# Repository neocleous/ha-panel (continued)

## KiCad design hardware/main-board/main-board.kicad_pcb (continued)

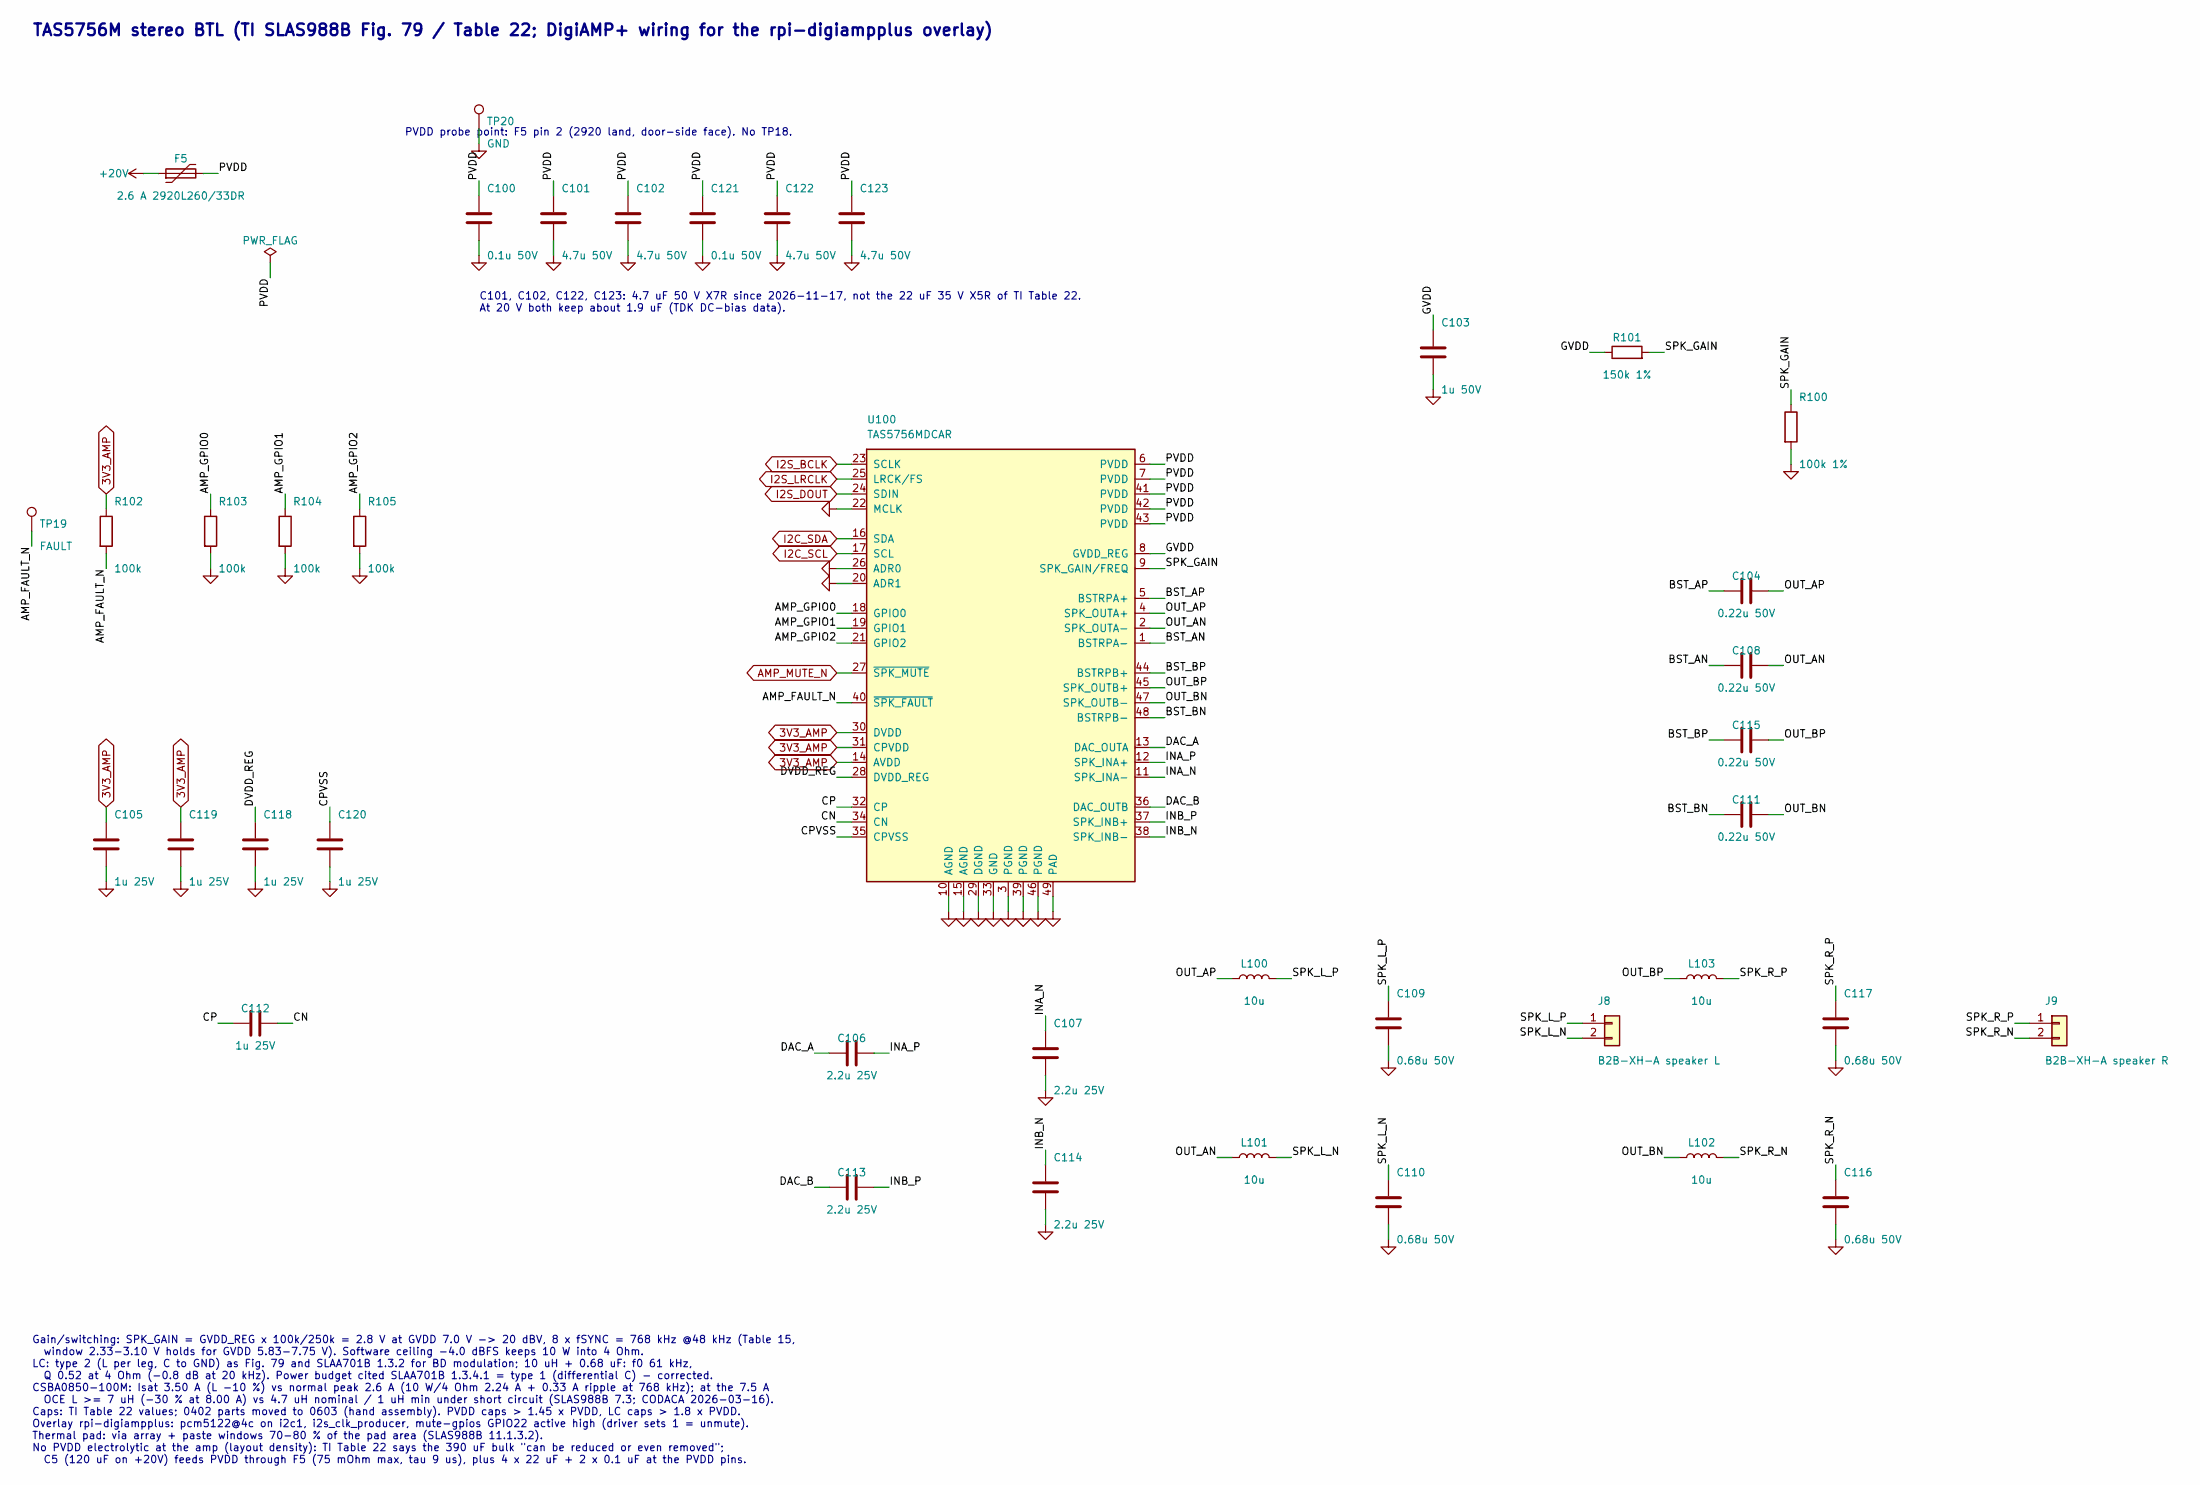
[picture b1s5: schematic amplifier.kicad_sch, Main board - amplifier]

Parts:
C100, C121: 0.1u 50V; C_0603_1608Metric; MPN CC0603KRX7R9BB104; DigiKey 311-1344-1-ND
C101, C102, C122, C123: 4.7u 50V; C_0805_2012Metric; MPN C2012X7R1H475K125AC; DigiKey 445-C2012X7R1H475K125ACCT-ND
C103: 1u 50V; C_0603_1608Metric; MPN UMK107AB7105KA-T; DigiKey 587-3247-1-ND
C104, C108, C111, C115: 0.22u 50V; C_0603_1608Metric; MPN CL10B224KB8NNNC; DigiKey 1276-CL10B224KB8NNNCCT-ND
C105, C112, C118, C119, C120: 1u 25V; C_0603_1608Metric; MPN CC0603KRX7R8BB105; DigiKey 311-1802-1-ND
C106, C107, C113, C114: 2.2u 25V; C_0603_1608Metric; MPN CC0603KRX7R7BB225; DigiKey 311-3490-1-ND
C109, C110, C116, C117: 0.68u 50V; C_0805_2012Metric; MPN CL21B684KBFVPNE; DigiKey 1276-7009-1-ND
F5: 2.6 A 2920L260/33DR; Fuse_2920_7451Metric; MPN 2920L260/33DR; DigiKey 18-2920L260/33DRCT-ND
J8: B2B-XH-A speaker L; JST_XH_B2B-XH-A_1x02_P2.50mm_Vertical; MPN B2B-XH-A; DigiKey 455-B2B-XH-A-ND
J9: B2B-XH-A speaker R; JST_XH_B2B-XH-A_1x02_P2.50mm_Vertical; MPN B2B-XH-A; DigiKey 455-B2B-XH-A-ND
L100, L101, L102, L103: 10u; L_Codaca_CSBA0850; MPN CSBA0850-100M; DigiKey 4044-CSBA0850-100MCT-ND
R100: 100k 1%; R_0603_1608Metric; MPN RMCF0603FT100K; DigiKey RMCF0603FT100KCT-ND
R101: 150k 1%; R_0603_1608Metric; MPN RC0603FR-07150KL; DigiKey 311-150KHRCT-ND
R102, R103, R104, R105: 100k; R_0603_1608Metric; MPN RMCF0603FT100K; DigiKey RMCF0603FT100KCT-ND
TP19: FAULT; TestPoint_Pad_D1.5mm
TP20: GND; TestPoint_Pad_D1.5mm
U100: TAS5756MDCAR; TI_DCA0048A_HTSSOP-48-1EP; MPN TAS5756MDCAR; DigiKey 296-40565-1-ND

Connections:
3V3_AMP: C105.1, C119.1, R102.1, U100.14 (AVDD), U100.30 (DVDD), U100.31 (CPVDD); also elsewhere on the board
+20V: F5.1; also elsewhere on the board
/Amplifier/AMP_FAULT_N: R102.2, TP19.1, U100.40 (~SPK_FAULT)
/Amplifier/AMP_GPIO0: R103.1, U100.18 (GPIO0)
/Amplifier/AMP_GPIO1: R104.1, U100.19 (GPIO1)
/Amplifier/AMP_GPIO2: R105.1, U100.21 (GPIO2)
/Amplifier/BST_AN: C108.1, U100.1 (BSTRPA-)
/Amplifier/BST_AP: C104.1, U100.5 (BSTRPA+)
/Amplifier/BST_BN: C111.1, U100.48 (BSTRPB-)
/Amplifier/BST_BP: C115.1, U100.44 (BSTRPB+)
/Amplifier/CN: C112.2, U100.34 (CN)
/Amplifier/CP: C112.1, U100.32 (CP)
/Amplifier/CPVSS: C120.1, U100.35 (CPVSS)
/Amplifier/DAC_A: C106.1, U100.13 (DAC_OUTA)
/Amplifier/DAC_B: C113.1, U100.36 (DAC_OUTB)
/Amplifier/DVDD_REG: C118.1, U100.28 (DVDD_REG)
/Amplifier/GVDD: C103.1, R101.1, U100.8 (GVDD_REG)
/Amplifier/INA_N: C107.1, U100.11 (SPK_INA-)
/Amplifier/INA_P: C106.2, U100.12 (SPK_INA+)
/Amplifier/INB_N: C114.1, U100.38 (SPK_INB-)
/Amplifier/INB_P: C113.2, U100.37 (SPK_INB+)
/Amplifier/OUT_AN: C108.2, L101.1, U100.2 (SPK_OUTA-)
/Amplifier/OUT_AP: C104.2, L100.1, U100.4 (SPK_OUTA+)
/Amplifier/OUT_BN: C111.2, L102.1, U100.47 (SPK_OUTB-)
/Amplifier/OUT_BP: C115.2, L103.1, U100.45 (SPK_OUTB+)
/Amplifier/PVDD: C100.1, C101.1, C102.1, C121.1, C122.1, C123.1, F5.2, U100.6 (PVDD), U100.7 (PVDD), U100.41 (PVDD), U100.42 (PVDD), U100.43 (PVDD)
/Amplifier/SPK_GAIN: R100.1, R101.2, U100.9 (SPK_GAIN/FREQ)
/Amplifier/SPK_L_N: C110.1, J8.2, L101.2
/Amplifier/SPK_L_P: C109.1, J8.1, L100.2
/Amplifier/SPK_R_N: C116.1, J9.2, L102.2
/Amplifier/SPK_R_P: C117.1, J9.1, L103.2
AMP_MUTE_N: U100.27 (~SPK_MUTE); also elsewhere on the board
GND: C100.2, C101.2, C102.2, C103.2, C105.2, C107.2, C109.2, C110.2, C114.2, C116.2, C117.2, C118.2, C119.2, C120.2, C121.2, C122.2, C123.2, R100.2, R103.2, R104.2, R105.2, TP20.1, U100.3 (PGND), U100.10 (AGND), U100.15 (AGND), U100.20 (ADR1), U100.22 (MCLK), U100.26 (ADR0), U100.29 (DGND), U100.33 (GND), U100.39 (PGND), U100.46 (PGND), U100.49 (PAD); also elsewhere on the board
I2C_SCL: U100.17 (SCL); also elsewhere on the board
I2C_SDA: U100.16 (SDA); also elsewhere on the board
I2S_BCLK: U100.23 (SCLK); also elsewhere on the board
I2S_DOUT: U100.24 (SDIN); also elsewhere on the board
I2S_LRCLK: U100.25 (LRCK/FS); also elsewhere on the board

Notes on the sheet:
TAS5756M stereo BTL (TI SLAS988B Fig. 79 / Table 22; DigiAMP+ wiring for the rpi-digiampplus overlay)
PVDD probe point: F5 pin 2 (2920 land, door-side face). No TP18.
C101, C102, C122, C123: 4.7 uF 50 V X7R since 2026-11-17, not the 22 uF 35 V X5R of TI Table 22. At 20 V both keep about 1.9 uF (TDK DC-bias data).
Gain/switching: SPK_GAIN = GVDD_REG x 100k/250k = 2.8 V at GVDD 7.0 V -> 20 dBV, 8 x fSYNC = 768 kHz @48 kHz (Table 15, window 2.33-3.10 V holds for GVDD 5.83-7.75 V). Software ceiling -4.0 dBFS keeps 10 W into 4 Ohm. LC: type 2 (L per leg, C to GND) as Fig. 79 and SLAA701B 1.3.2 for BD modulation;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

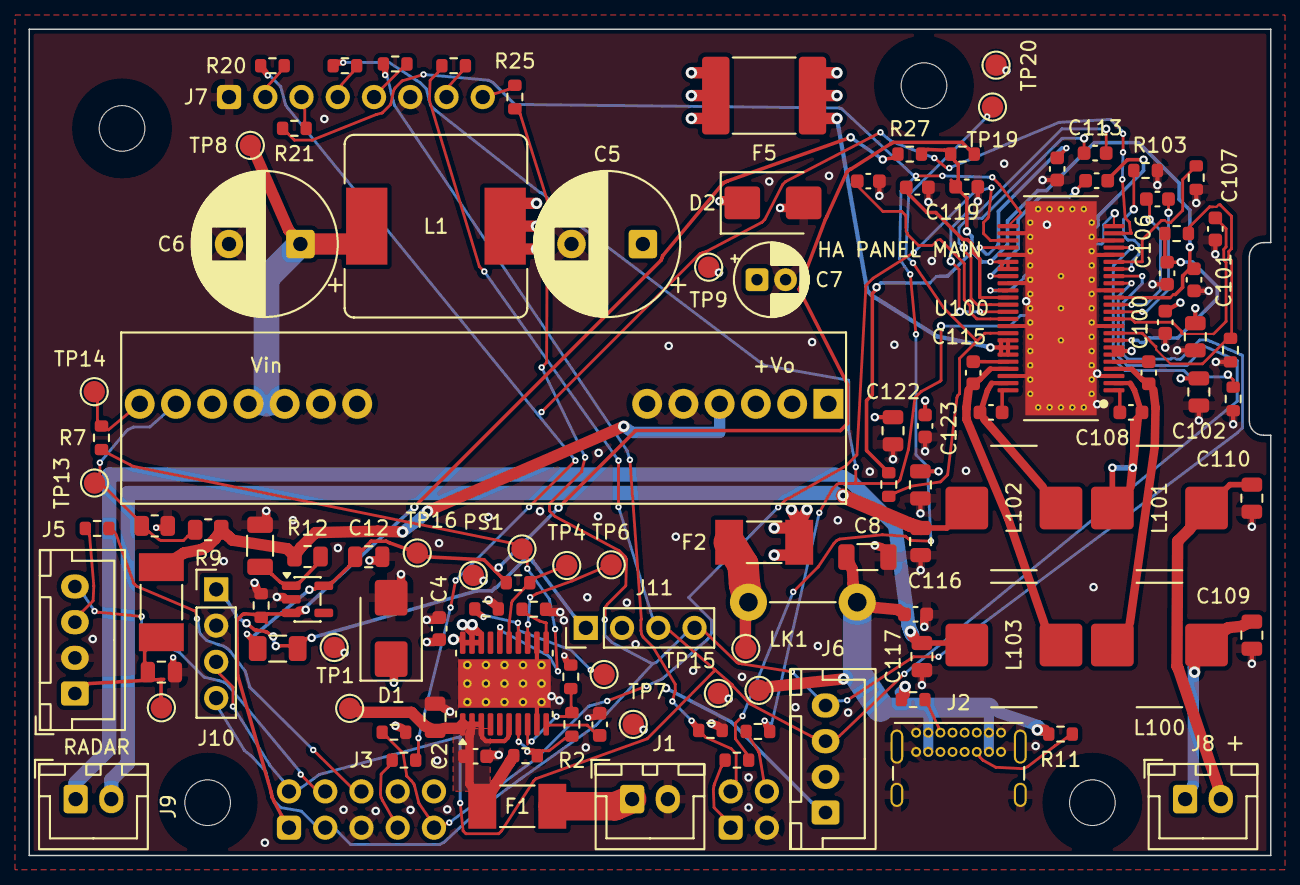
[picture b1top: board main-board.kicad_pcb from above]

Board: 4 copper layers, 87.0 x 57.9 mm, 120 parts (0 on the bottom side), 74 nets.

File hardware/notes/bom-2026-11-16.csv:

Board,Boards per set,References,Fitted,Value,Package,Maker,Maker's part number,Qty per board,Qty per set,DigiKey number,Note
Main board rev 3.2,1,"C1, C10",yes,1u 50V,0805,KYOCERA AVX,08055C105KAT2A,2,2,478-KGM21AR71H105KUCT-ND,
Main board rev 3.2,1,"C2, C4, C9, C100, C121",yes,100n 50V,0603,Yageo,CC0603KRX7R9BB104,5,5,311-1344-1-ND,
Main board rev 3.2,1,C3,yes,47n 50V,0603,Samsung,CL10B473KB8NNNC,1,1,1276-1063-1-ND,
Main board rev 3.2,1,"C5, C6",yes,120u 63V,"radial Ø10, pitch 5.0, through-hole",Panasonic,EEU-FR1J121B,2,2,P15289CT-ND,
Main board rev 3.2,1,C7,yes,22u 35V,"radial Ø5, pitch 2.0, through-hole",Würth,860160572003,1,1,732-9541-1-ND,
Main board rev 3.2,1,"C8, C11",yes,10u 25V,1206,KEMET,C1206C106K4RACTU,2,2,399-C1206C106K4RACTUCT-ND,
Main board rev 3.2,1,C12,yes,4.7u 16V,0805,Samsung,CL21B475KOFNNNE,1,1,1276-2873-1-ND,
Main board rev 3.2,1,"C101, C102, C122, C123",yes,22u 35V,0805,Cal-Chip,GMC21X5R226M35NT,4,4,4713-GMC21X5R226M35NTCT-ND,
Main board rev 3.2,1,C103,yes,1u 50V,0603,Taiyo Yuden,UMK107AB7105KA-T,1,1,587-3247-1-ND,
Main board rev 3.2,1,"C104, C108, C111, C115",yes,0.22u 50V,0603,Samsung,CL10B224KB8NNNC,4,4,1276-CL10B224KB8NNNCCT-ND,
Main board rev 3.2,1,"C105, C112, C118–C120",yes,1u 25V,0603,Yageo,CC0603KRX7R8BB105,5,5,311-1802-1-ND,
Main board rev 3.2,1,"C106, C107, C113, C114",yes,2.2u 25V,0603,Yageo,CC0603KRX7R7BB225,4,4,311-3490-1-ND,
Main board rev 3.2,1,"C109, C110, C116, C117",yes,0.68u 50V,0805,Samsung,CL21B684KBFVPNE,4,4,1276-7009-1-ND,
Main board rev 3.2,1,D1,yes,SMBJ22A,SMB (DO-214AA),Littelfuse,SMBJ22A,1,1,SMBJ22ALFCT-ND,
Main board rev 3.2,1,D2,yes,SMBJ6.0A-E,SMB (DO-214AA),Littelfuse,SMBJ6.0A-E,1,1,18-SMBJ6.0A-ECT-ND,
Main board rev 3.2,1,F1,yes,5 A 0453005.MR,"NANO2, SMD",Littelfuse,0453005.MR,1,1,F3139CT-ND,
Main board rev 3.2,1,F2,yes,10 A 0453010.MR,"NANO2, SMD",Littelfuse,0453010.MR,1,1,F3141CT-ND,
Main board rev 3.2,1,F3,yes,1 A 0453001.MR,"NANO2, SMD",Littelfuse,0453001.MR,1,1,F3137CT-ND,
Main board rev 3.2,1,F4,yes,0.2 A 0ZCJ0020FF2E,1206,Bel,0ZCJ0020FF2E,1,1,5923-0ZCJ0020FF2ECT-ND,
Main board rev 3.2,1,F5,yes,2.6 A 2920L260/33DR,2920,Littelfuse,2920L260/33DR,1,1,18-2920L260/33DRCT-ND,
Main board rev 3.2,1,"J1, J8, J9",yes,B2B-XH-A,"JST XH, 2 pins, through-hole",JST,B2B-XH-A,3,3,455-B2B-XH-A-ND,
Main board rev 3.2,1,J2,yes,USB4085-GF-A,"USB-C socket, through-hole",GCT,USB4085-GF-A,1,1,2073-USB4085-GF-ACT-ND,
Main board rev 3.2,1,"J5, J6",yes,B4B-XH-A,"JST XH, 4 pins, through-hole",JST,B4B-XH-A,2,2,455-B4B-XH-A-ND,
Main board rev 3.2,1,"J10, J11",yes,1x04 header,"pin header 1 × 4, 2.54 pitch, through-hole",generic,"generic 1 x 4 male pin header, 2.54 mm pitch, THT, vertical",2,2,,none - not in any basket; chosen with the parts list in step 5 (rev 3: one 1 x 4 header per sensor lead)
Main board rev 3.2,1,L1,yes,15u SRR1260,"SRR1260, SMD",Bourns,SRR1260-150M,1,1,SRR1260-150MCT-ND,
Main board rev 3.2,1,L100–L103,yes,10u,"CSBA0850, SMD",CODACA,CSBA0850-100M,4,4,4044-CSBA0850-100MCT-ND,
Main board rev 3.2,1,LK1,yes,wire link,"two Ø1.3 holes, 7.62 apart",,,1,1,,
Main board rev 3.2,1,PS1,yes,NID100-5,"SIP-13 module, through-hole",Mean Well,NID100-5,1,1,1866-NID100-5-ND,
Main board rev 3.2,1,R1,yes,412k 1%,0603,Yageo,RC0603FR-07412KL,1,1,311-412KHRCT-ND,
Main board rev 3.2,1,R2,yes,9.09k 1%,0603,Yageo,RC0603FR-079K09L,1,1,311-9.09KHRCT-ND,
Main board rev 3.2,1,R3,yes,22.1k 1%,0603,Yageo,RC0603FR-0722K1L,1,1,311-22.1KHRCT-ND,
Main board rev 3.2,1,R4,yes,5.49k 1%,0603,Yageo,RC0603FR-075K49L,1,1,311-5.49KHRCT-ND,
Main board rev 3.2,1,"R5, R10, R11",yes,10k 1%,0603,Stackpole,RMCF0603FT10K0,3,3,RMCF0603FT10K0CT-ND,
Main board rev 3.2,1,"R6, R13, R17, R18, R100, R102–R105",yes,100k 1%,0603,Stackpole,RMCF0603FT100K,9,9,RMCF0603FT100KCT-ND,
Main board rev 3.2,1,"R7, R14–R16, R26",yes,0R,0603,Yageo,RC0603JR-070RL,5,5,311-0.0GRCT-ND,
Main board rev 3.2,1,R12,yes,2.2R,0805,Stackpole,RMCF0805FT2R20,1,1,RMCF0805FT2R20CT-ND,
Main board rev 3.2,1,R19,yes,4.7k,0603,Yageo,RC0603FR-074K7L,1,1,311-4.70KHRCT-ND,
Main board rev 3.2,1,R101,yes,150k 1%,0603,Yageo,RC0603FR-07150KL,1,1,311-150KHRCT-ND,
Main board rev 3.2,1,U1,yes,TPS16630PWPT,"HTSSOP-20 with centre pad, 0.65 pitch",TI,TPS16630PWPT,1,1,296-TPS16630PWPTCT-ND,
Main board rev 3.2,1,U2,yes,TPS70933QDBVRQ1,SOT-23-5,TI,TPS70933QDBVRQ1,1,1,296-40931-1-ND,
Main board rev 3.2,1,U100,yes,TAS5756MDCAR,"HTSSOP-48 with centre pad, 0.5 pitch",TI,TAS5756MDCAR,1,1,296-40565-1-ND,
Main board rev 3.2,1,"R8, R9",no,DNP (bench),0805,,,2,0,,
Main board rev 3.2,1,"R20–R25, R27",no,0R,0603,Yageo,RC0603JR-070RL,7,0,311-0.0GRCT-ND,
Mic strip,2,C1,yes,10u 10V,0603,Taiyo Yuden,EMK107BBJ106MA-T,1,2,587-3238-1-ND,
Mic strip,2,"C2, C3",yes,100n 50V,0603,Yageo,CC0603KRX7R9BB104,2,4,311-1344-1-ND,
Mic strip,2,D1–D3,yes,ESD321,SOD-523,TI,ESD321DYAR,3,6,296-ESD321DYARCT-ND,
Mic strip,2,MK1,yes,IM69D120V01,PG-LLGA-5-1 (MEMS microphone),Infineon,IM69D120V01XTSA1,1,2,IM69D120V01XTSA1CT-ND,
Mic strip,2,R1,yes,100R,0603,Stackpole,RMCF0603FT100R,1,2,RMCF0603FT100RCT-ND,
Mic strip,2,R2,yes,100k,0603,Stackpole,RMCF0603FT100K,1,2,RMCF0603FT100KCT-ND,
Mic strip,2,R4,yes,33R,0603,Stackpole,RMCF0603FT33R0,1,2,RMCF0603FT33R0CT-ND,
Mic strip,2,R5,yes,0R,0603,Yageo,RC0603JR-070RL,1,2,311-0.0GRCT-ND,
Mic strip,2,U1,yes,SN74LVC1G17DCKR,SC-70-5,TI,SN74LVC1G17DCKR,1,2,296-11934-1-ND,
Touch board rev D,1,C1,yes,100n 50V,0603,Yageo,CC0603KRX7R9BB104,1,1,311-1344-1-ND,
Touch board rev D,1,C2,yes,10u 10V,0603,Taiyo Yuden,EMK107BBJ106MA-T,1,1,587-3238-1-ND,
Touch board rev D,1,R1–R4,yes,4.7k,0603,Yageo,RC0603FR-074K7L,4,4,311-4.70KHRCT-ND,
Touch board rev D,1,U1,yes,AT42QT1070-SSU,"SOIC-14, 1.27 pitch",Microchip,AT42QT1070-SSUR,1,1,,none - from Daniel's stock (D56)

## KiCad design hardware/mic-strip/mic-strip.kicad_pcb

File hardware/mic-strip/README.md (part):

# Mic strip

A small board that carries one MEMS microphone (Infineon IM69D120) in the panel's top cap. The panel has two, left and
right: two boards of this one design. Each strip is wired by a five-way lead to the ReSpeaker Lite, the panel's voice
front end, in place of the ReSpeaker's own microphones.

**State (2026-11-21):** rev 3, fab set issued on 2026-11-21 after the pre-order review: the vias are out of the soldered
pads and the silk lines are 0.15 wide ("The board"). The set of 2026-11-09 (rev 1) is in `fab/superseded/` and must not
be ordered. Rev 2 (31.4 long, 2026-11-19) was not built; its name is not reused.
In the cap the strip is held by a printed clamp that presses on two areas of its back; its two holes only locate it
on the cap's pins ("The board"). Not built or tested yet.

**Checks (KiCad 9.0.9, 2026-11-21):** schematic 0 errors, 0 warnings (`erc-report.txt`); board (all severities)
0 violations, 0 unconnected, 0 footprint errors, schematic parity clean (`drc-report.txt`). The check "footprint differs
from library" is set to ignore: U1's and MK1's silk marks at the board edge were removed on purpose. A fresh export
gives the zip of 2026-11-21 file for file.

## Files
| File | What |
|---|---|
| `mic-strip.kicad_pro`, `.kicad_sch`, `.kicad_pcb` | the design, KiCad 9.0.9. Project libraries: `lib/ha_panel.kicad_sym` (IM69D120) and `lib/ha_panel.pretty` (IM69D120 land pattern, 5-pad wire column, and the footprint the two locating holes are drawn with) |
| `mic-strip-schematic.pdf` | the schematic |
| `mic-strip-assembly.pdf` | the assembly drawing (the back, as seen from the back) |
| `mic-strip-3d.png`, `mic-strip-copper-F-B.png` | a render of rev 1 (front = gasket side, back = parts; the moved vias do not show at its size) and both copper layers of rev 3 (back mirrored) |
| `erc-report.txt`, `drc-report.txt` | KiCad's checks |
| [`fab/`](fab/) | **what goes to JLC:** `mic-strip-rev3-jlc-2026-11-21.zip`, the files unzipped in `gerbers/`, the hole list, the check of the set, and the order sheet; `superseded/` holds rev 1's set, which must not be ordered |

## How to order
- **Upload** `fab/mic-strip-rev3-jlc-2026-11-21.zip` to JLC as a bare board. sha256
  `0e378603bf06f547f44f3cb741d6ad13222e0321c87d36a35d0614bcfe94b095`. It replaces the zip of 2026-11-09.
- **Options in short:** 2 layers, 28 × 6 mm, 0.8 mm, black with white silkscreen, ENIG (the page's default for 2 layers
  is OSP: change it), vias tented, deburring on, via class "0.3mm/(0.4/0.45mm)", 5 pieces (2 needed). Every option:
  [`fab/ORDER-SHEET.md`](fab/ORDER-SHEET.md).
- **Stencil:** since 2026-11-21 the strip's back paste is on the touch board's stencil, its own line
  ([`../stencil/`](../stencil/)). Don't tick the stencil box on the strip line.

## Parts
Every part with its DigiKey line: [`../notes/bom-2026-11-17.md`](../notes/bom-2026-11-17.md), section "Mic strip".

| Ref | Part | Why |
|---|---|---|
| J1 | 5 SMD wire pads 2.0 × 0.7, 1.1 mm pitch, one column across the strip | A JST BM05B-SRSS-TB connector (8.89 mm courtyard) does not fit beside the parts, so the lead is soldered on. Lead: JST A05SR05SR30K305B with both housings cut off, conductors in cable order **1 VDD, 2 GND, 3 CLK, 4 SEL, 5 DATA**; hot-melt strain relief over the pads. The pads are also the test points. |
| D1–D3 | TI ESD321DYAR, SOD-523 | ESD protection on VDD, CLK and DATA next to the pads. 0.9 pF typ / 1.1 pF max, VRWM 3.6 V above the 3.3 V lines. **Pin 1 = GND, pin 2 = IO**, the reverse of the TPD1E05U06 it replaced, so the footprints are turned 180°. Pin 1 is the end marked by the dot (TI marks the DYA pin 1 with a circular notch, not a line); it goes to the closed end of the silk bracket, the GND pad at x 19.8. |
| R1 | 100 Ω 0603 | VDD RC filter with C1: f_c = 159 Hz; drop ≈ 0.1 V at the microphone's 980 µA. |
| C1, C2 | 10 µF 10 V X5R 0603, 100 nF 50 V X7R 0603 | Microphone decoupling; C2 next to MK1's VDD pin. |
| U1 | TI SN74LVC1G17DCKR, SC-70-5 | Schmitt buffer that re-drives CLK next to the microphone. C3 100 nF at VCC. To bypass it on the bench: remove U1 and bridge its pads 2–4 with wire. |
| R2 | 100 kΩ 0603 | Weak pull-down on the buffer input (CLK may be tri-stated when muted — inference). |
| MK1 | Infineon IM69D120V01XTSA1 | Bottom port, −26 dBFS ±1, SNR 69 dB(A), 3.072 MHz inside its 2.9–3.3 MHz range, clock duty 48–52 %, 980 µA typ, VDD 1.62–3.6 V (datasheet rev 1.0, 2017-12-20). |
| R4 | 33 Ω 0603 | DATA source termination (100 Ω as a bench alternative). |
| R5 | 0 Ω 0603 | **Left/right from the lead's SEL wire,** strapped at the ReSpeaker end: GND = left, VDD = right. Must be fitted on both strips; there is no strap on the board. |

## The board
- **28 × 6 × 0.8 mm, 2 layers.** x = 0 at the outer (port) end. Every part sits on the **back** (inner side); the front
  faces the 1.0 mm gasket and carries only the ground pour and short crossings.
- **Port:** unplated Ø0.8 at (2.0, 3.0), under MK1's sound port.
- **Locating holes:** unplated Ø2.0 at (7.5, 3.0) and (26.0, 3.0). They sit on the cap's Ø1.8 pins; nothing is melted or
  screwed through them. On the back a Ø3.6 ring round each hole has no copper. In the KiCad files the holes keep the
  footprint `HeatStake_D2.0mm_Head3.6mm` and the rings the zone names "stake head 1" and "stake head 2", from when the
  pins were to be melted; only the names are left.
- **Press areas for the clamp's toes** (back, symmetric about y 3.0, one over each hole):
  - outer x 6.5–8.5 and inner x 25.7–27.7, both y 2.0–4.0, for toes of 2.0 × 2.0;
  - nothing under them but the holes; a corner of the inner area lies over ground pour under soldermask;
  - nearest: U1's pad 1.120 from the outer area, C2 1.275, R4 1.445; J1's pads 1.650 from the inner area, which ends 0.3
    from the board's inner end;
  - room to move or grow at the same clearances (1.0 to any part, 1.5 to J1): x 6.23–8.62 and 25.56–27.70, out to 0.3
    from the long edges.
- **Heights on the back,** the makers' maximums without the solder under each part: MK1 1.3, the tallest, at the outer
  end; C2 0.9 beside it; between the press areas U1 1.1, C1 1.0, C3 0.9, D1–D3 0.77, the resistors 0.55. The lead's
  wires at J1 are 0.54–0.58 across their insulation.
- One design for both sides: the left strip is the right one turned 180° in the cap's plane (port end outward, gasket
  side up).
- **Rules:** tracks 0.2 (0.25–0.3 for supply and ground), clearance 0.15, copper to edge 0.3; vias 0.5/0.3, ring 0.10;
  hole clearance 0.25, hole to hole 0.25;
  silk lines 0.15, JLC's minimum (0.12 until 2026-11-21).
- **Vias: 24 × 0.5/0.3, all tented.** On 2026-11-09, 28 × 0.45/0.2 became 25 × 0.5/0.3: JLC's order page states its free
  0.2 mm holes only for multilayer boards; 0.3 mm holes are the free class on 2 layers.
- **Vias out of the soldered pads (2026-11-21).** Thirteen via holes lay inside pads that take solder, one wholly inside
  MK1's SELECT pad, and one more ended 0.014 from U1's pin 4. Molten solder runs into an open hole, and the joints under
  MK1 cannot be seen or reworked. Thirteen of these vias moved 0.21 to 0.80, each joined to its pad by a short track on
  the back; the front tracks followed. U1's pin 3 lost its via: the pin already reaches the ground via at (12.925, 2.525)
  through its track to R2.2. Placement, parts, pads, outline, holes and port did not change, and no via lies in the clamp's
  press areas or their room (nearest 0.41 from the outer room, 0.59 from the outer area).
  - Every via hole is now **0.217 or more** from the opening of every pad that takes paste. J1.2's ground via still lies
    partly in its wire pad, which takes no paste; it is left as it is.
  - Achieved: ring 0.10; via hole to hole ≥ 0.40; via hole to unplated hole ≥ 0.86; via hole to other-net track ≥ 0.27
    and to other-net pad ≥ 0.27 (rule 0.25). JLC's figures: [`../notes/jlc-fab.md`](../notes/jlc-fab.md).

## How to assemble
Build two identical strips. Drawing: `mic-strip-assembly.pdf`. One hotplate pass, parts side up.

**Before you start**
- **Paste:** the same Sn63/Pb37 no-clean as the main board, through the stencil: the strip's pattern on the touch
  board's sheet ([`../stencil/`](../stencil/)). The strip lies front-down in a jig that holds it flush with the
  surface round it, so the sheet lies flat: a pocket of the strip's size, as deep as the strip and the Kapton of step
  1, or spare strips laid round it. **No jig is drawn yet.**
- **D1–D3 (ESD321DYAR) are moisture-sensitive, level 3:** once their bag is open, solder them within 168 hours at 30 °C /
  60 % humidity or less (TI's package information); open the bag on the day, or bake them per J-STD-033 first.
- **Bare strip:** hold it against the light: the Ø0.8 port hole must be open. Meter: VDD–GND (J1 pads 1–2) open.
- **The port:** Infineon's datasheet (rev 1.0) gives only the reflow qualification: 3 reflows, peak 260 °C, IPC/JEDEC
  J-STD-020D-01; it has no handling, flux or washing rules. Other makers' bottom-port MEMS guides agree on these:
  TDK/InvenSense: water must not reach the port when washing, no blow-off, no ultrasonic cleaning; InvenSense AN-100: the
  port is sensitive to solder flux; ST: seal the port with tape during soldering. So: no-clean paste, **no washing, no
  IPA or air near the port**, and Kapton tape over the hole on the front while soldering.

**Order**
1. Kapton over the port hole on the front (gasket side).
2. Strip front-down in the jig; paste the back through the strip's pattern, keeping the squeegee off the touch
   board's pattern (or tape it over). The sheet has no opening over the port; check that no paste lies in the port
   hole or inside the microphone's ring.
3. Place:
   - D1–D3 ESD321: pin 1 = GND (dot or notch on the body), at the closed end of the silk bracket;
   - C1 10 µF, C2 100 nF, C3 100 nF;
   - R1 100 Ω, R2 100 kΩ, R4 33 Ω, R5 0 Ω (**required**);
   - U1 SN74LVC1G17 (pin 1 at the chamfer);
   - MK1 last, lid up, port over the hole. Handle it by the lid only.
4. Hotplate with the front (gasket side) down, the same profile as the main board
   ([`../main-board/README.md`](../main-board/README.md)). One pass: the IM69D120 is qualified for 3 reflows, and a
   rework pass counts as one.
5. Remove the Kapton when the strip is cool. Leave the no-clean residue.
6. **Checks, meter only:**
   - D1–D3 in diode mode: red on the GND pad, black on the signal pad → conducts; reversed → open.
   - VDD–GND not shorted.
   - R5 present.
7. **Lead:** JST A05SR05SR30K305B with both housings cut off, free length 230 mm (harness list of 2026-11-14).
   - Strip end: solder the conductors in cable order to J1 pads 1–5: 1 VDD, 2 GND, 3 CLK, 4 SEL, 5 DATA. Pad 1 is at
     the top in the drawing.
   - **The wires lie on their pads with their tips toward the inner end, so that the lead leaves J1 over its outer end**
     (toward D1–D3), never over the inner end: the inner press area starts 1.65 beyond it.
   - Lay the five wires toward the long edge that faces the screen in the cap, and lead them off the board there, over
     D1–D3 (x 19 to 22). Nothing of the lead goes toward the other long edge: the clamp is on that side.
   - Hot-melt strain relief over the pads: a thin bead, no higher than U1 (1.1 from the board) and not past the pads'
     inner end (x 24.05).
   - ReSpeaker end, by function: VDD → pad 1, CLK → 2, DATA → 3, GND → 4 (and 6), SEL → 5. SEL is static and sits
     between CLK and DATA in the cable.
   - SEL strap at the ReSpeaker end: one strip to GND (left), the other to VDD (right).

## Bring-up
No stand-alone power test. With both strips on the ReSpeaker, run `arecord -l`. The pass mark is the audio bench test:
click count, noise floor and false-reject rate. If it fails, the options are: bypass U1 (remove it, wire pads 2–4), or
change R4 from 33 Ω to 100 Ω.

## How it changed
Rev 3 (2026-11-21): the vias out of the soldered pads and silk 0.15, after the pre-order review; nothing else moved.
Rev 2 (31.4 long, holes for M2 screws, 2026-11-19) was not built: the clamp took its place, and rev 1 stood until rev 3.
During the design the JST connector, the on-board strap JP1 and four test pads were dropped for the wire pads, R3 (a
0 Ω bypass) for space; the MSM261DHP006 microphone was replaced by the IM69D120, and the TPD1E05U06DYAR diodes by the
ESD321DYAR (DigiKey: 0 in stock, 26 weeks, 2026-11-08). The scripts that generated the schematic and the layout are in
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
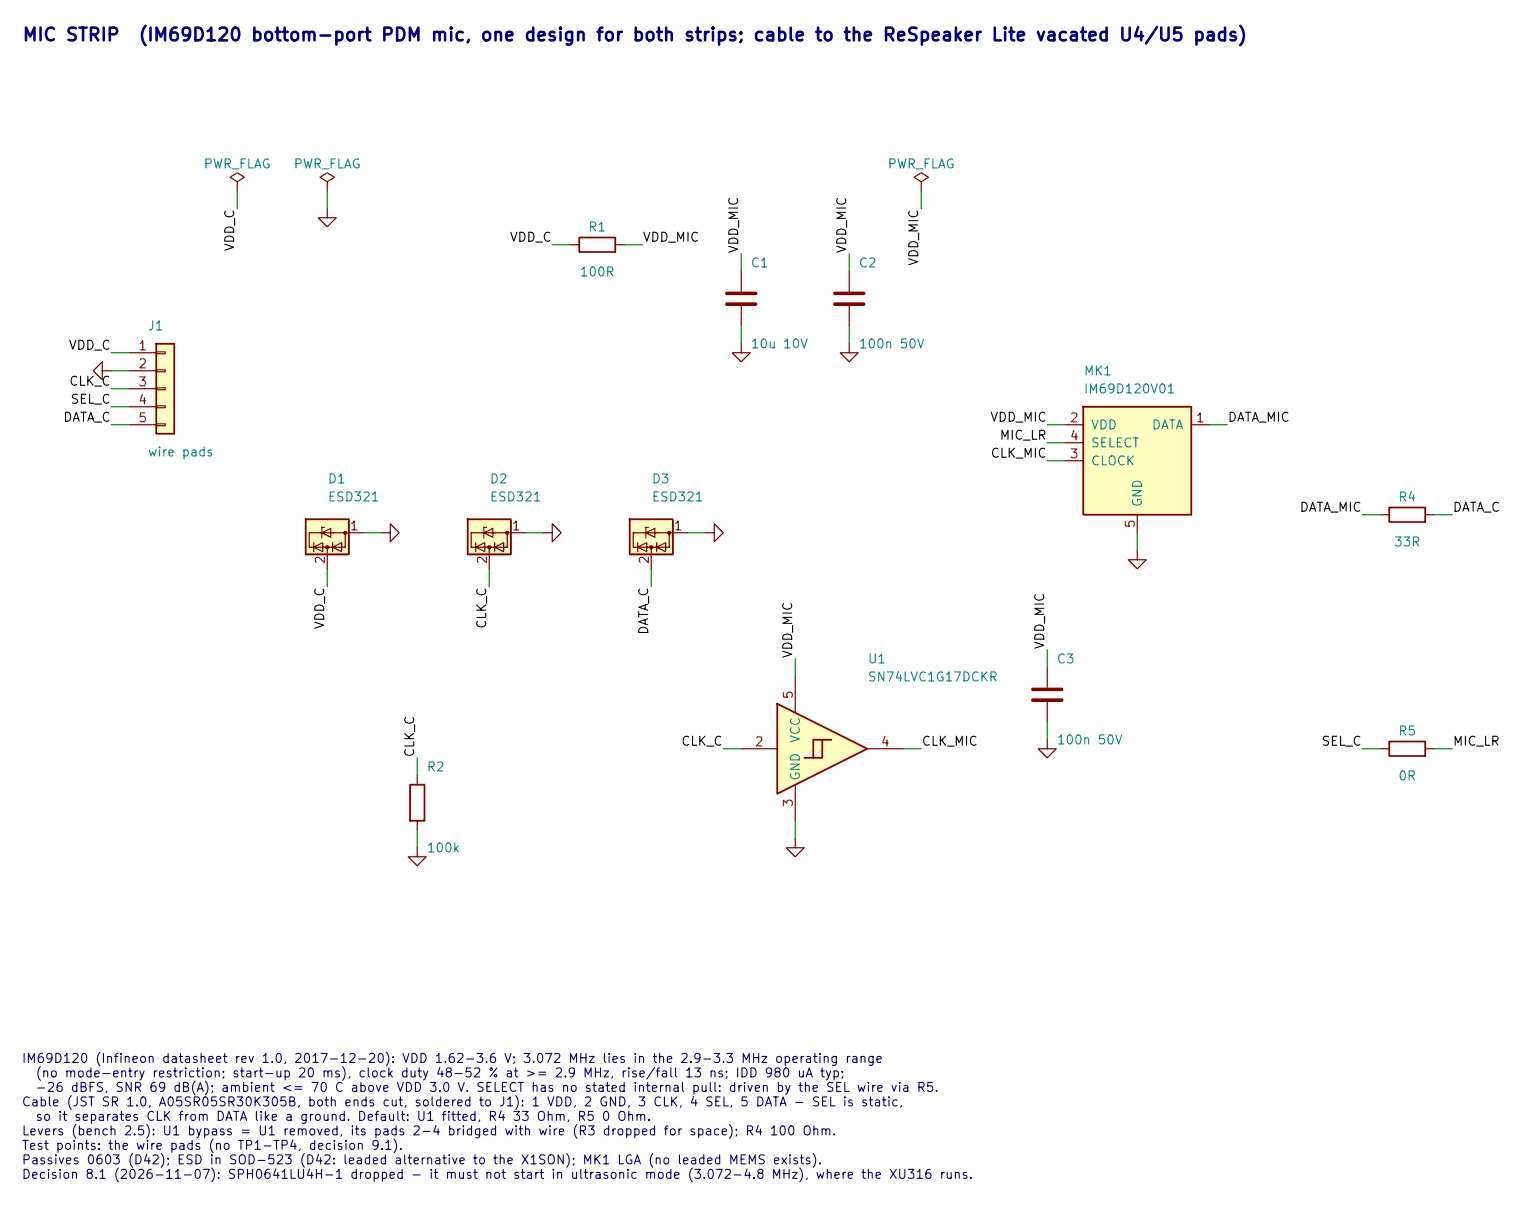
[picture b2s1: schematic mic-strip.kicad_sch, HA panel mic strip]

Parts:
C1: 10u 10V; C_0603_1608Metric; MPN EMK107BBJ106MA-T; DigiKey 587-3238-1-ND
C2, C3: 100n 50V; C_0603_1608Metric; MPN CC0603KRX7R9BB104; DigiKey 311-1344-1-ND
D1, D2, D3: ESD321; D_SOD-523; MPN ESD321DYAR; DigiKey 296-ESD321DYARCT-ND
J1: wire pads; WirePads_1x05_P1.10mm_2.0x0.7mm
MK1: IM69D120V01; Infineon_IM69D120_PG-LLGA-5-1; MPN IM69D120V01XTSA1; DigiKey IM69D120V01XTSA1CT-ND
R1: 100R; R_0603_1608Metric; MPN RMCF0603FT100R; DigiKey RMCF0603FT100RCT-ND
R2: 100k; R_0603_1608Metric; MPN RMCF0603FT100K; DigiKey RMCF0603FT100KCT-ND
R4: 33R; R_0603_1608Metric; MPN RMCF0603FT33R0; DigiKey RMCF0603FT33R0CT-ND
R5: 0R; R_0603_1608Metric; MPN RC0603JR-070RL; DigiKey 311-0.0GRCT-ND
U1: SN74LVC1G17DCKR; SOT-353_SC-70-5; MPN SN74LVC1G17DCKR; DigiKey 296-11934-1-ND

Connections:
/CLK_C: D2.2 (I/O), J1.3, R2.1, U1.2
/CLK_MIC: MK1.3 (CLOCK), U1.4
/DATA_C: D3.2 (I/O), J1.5, R4.2
/DATA_MIC: MK1.1 (DATA), R4.1
/MIC_LR: MK1.4 (SELECT), R5.2
/SEL_C: J1.4, R5.1
/VDD_C: D1.2 (I/O), J1.1, R1.1
/VDD_MIC: C1.1, C2.1, C3.1, MK1.2 (VDD), R1.2, U1.5 (VCC)
GND: C1.2, C2.2, C3.2, D1.1 (GND), D2.1 (GND), D3.1 (GND), J1.2, MK1.5 (GND), R2.2, U1.3 (GND)

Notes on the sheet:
MIC STRIP (IM69D120 bottom-port PDM mic, one design for both strips; cable to the ReSpeaker Lite vacated U4/U5 pads)
IM69D120 (Infineon datasheet rev 1.0, 2017-12-20): VDD 1.62-3.6 V; 3.072 MHz lies in the 2.9-3.3 MHz operating range (no mode-entry restriction; start-up 20 ms), clock duty 48-52 % at >= 2.9 MHz, rise/fall 13 ns; IDD 980 uA typ; -26 dBFS, SNR 69 dB(A); ambient <= 70 C above VDD 3.0 V. SELECT has no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

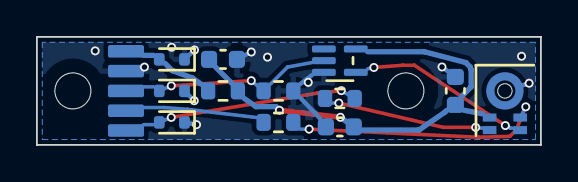
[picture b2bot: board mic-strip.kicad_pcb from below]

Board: 2 copper layers, 28.0 x 6.0 mm, 15 parts (13 on the bottom side), 9 nets.

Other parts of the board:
HS1, HS2: heat stake; HeatStake_D2.0mm_Head3.6mm

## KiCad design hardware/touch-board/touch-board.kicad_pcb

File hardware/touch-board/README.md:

# Touch board, rev E

The panel's four touch keys. Four copper electrodes on the front face sit behind the shell's chin; an AT42QT1070 on the
back reads them and talks to the Pi over I²C (address 0x1B) through a four-wire lead from the main board's socket J6.

It replaces rev C ([`../rev-c/`](../rev-c/), the touch board of the first panel) with the same 90 × 44 × 1.6 outline,
R2 corners, no holes except tented vias and a flat front.

**State (2026-11-21):** rev E, fab set issued on 2026-11-21: rev D with every silk line 0.15 wide and the back's text
reading `rev E 2026-11-21`; copper, mask and paste are rev D's. The set of 2026-11-09 (rev D) is in `fab/superseded/`.
Not built or tested yet.

**Checks (KiCad 9.0.9, 2026-11-21):** schematic 0 errors, 0 warnings (`erc-report.txt`); board (all severities, with
schematic parity) 0 violations, 0 unconnected, 0 footprint errors (`drc-report.txt`). A fresh export gives the zip of
2026-11-21 file for file.

## Files
| File | What |
|---|---|
| `touch-board.kicad_pro`, `.kicad_sch`, `.kicad_pcb` | the design, KiCad 9.0.9; `lib/` holds the project's symbol and footprints |
| `touch-board-schematic.pdf` | the schematic |
| `touch-board-assembly.pdf` | the assembly drawing (the back, as seen from the back) |
| `touch-board-front.png`, `touch-board-back.png` | renders of both faces, rev D: on rev E the back's text reads `rev E 2026-11-21` |
| `erc-report.txt`, `drc-report.txt` | KiCad's checks |
| [`fab/`](fab/) | **what goes to JLC:** `touch-board-revE-jlc-2026-11-21.zip`, the files unzipped in `gerbers/`, the hole list, the check of the set, and the order sheet; `superseded/` holds rev D's set |

## How to order
- **Upload** `fab/touch-board-revE-jlc-2026-11-21.zip` to JLC as a bare board. sha256
  `12641c710499f8dab67cd457623986f8389a1c9a527aa9ff06c9db64083fa4ec`. It replaces the zip of 2026-11-09.
- **Options in short:** 2 layers, 90 × 44 mm, 1.6 mm, black with white silkscreen, ENIG (the page's default for 2 layers
  is OSP: change it), vias tented, 5 pieces (1 needed). Every option: [`fab/ORDER-SHEET.md`](fab/ORDER-SHEET.md).
- **Paste:** the touch board's back pattern is on a 100 × 100 stencil it shares with the mic strip's pattern, a
  separate line ([`../stencil/`](../stencil/)). Don't tick the stencil box on the touch-board line.

## Parts
Every part with its DigiKey line: [`../notes/bom-2026-11-17.md`](../notes/bom-2026-11-17.md), section "Touch board rev D" (rev E changed no part).

| Ref | Part | Note |
|---|---|---|
| U1 | Microchip AT42QT1070-SSUR, SOIC-14 | from stock; not a DigiKey line |
| C1 | Yageo CC0603KRX7R9BB104, 100 nF 50 V X7R | DigiKey 311-1344-1-ND, a line shared with the main board and the strip |
| C2 | Taiyo Yuden EMK107BBJ106MA-T, 10 µF 16 V X5R | DigiKey 587-3238-1-ND, a line shared with the strip |
| R1–R4 | Yageo RC0603FR-074K7L, 4.7 kΩ 1 % | DigiKey 311-4.70KHRCT-ND, a line shared with the main board |
| J1 | bare wire pads | — |
| E0–E3 | copper electrodes | — |

## The design
| Item | Value | Source |
|---|---|---|
| Controller | AT42QT1070 SOIC-14, comms (I²C) mode, address 0x1B; MODE (pin 2) to GND; RESET, CHANGE, KEY4–6 open | Atmel 9596C–AT42–05/2013 table 1-1 |
| Electrodes | 4 × 16 × 16 mm, r 2, front copper under the mask; centres front-view X 9/33/57/81, Y 13 | QTAN0062 §2.3: electrode ≥ 4 × panel thickness; panel ≈ 2.5 wall + 0.7 cloth = 3.2 mm (from the model, not measured) → ≥ 12.8 mm. Rev C: Ø12 |
| Key order | seen from the front, left to right **KEY0, KEY1, KEY2, KEY3**, the same order as rev C, so the key map in the sensor daemon's `at42qt1070.py` applies unchanged | |
| Series resistors | R1–R4 4.7 kΩ 0603, next to U1 | datasheet §3.1 |
| Decoupling | C1 100 nF + C2 10 µF 0603 | |
| HOST pads | J1, SMD wire pads 2 × 3 mm at 3.5 pitch on the back, front-view (33, 39.8): VCC, GND, SDA, SCL (labelled); lead from main board J6 | |
| Sensors | none: the BME680 and VEML6030 leads land on the main board (J10, J11); the VL53L0X of rev C is dropped | |
| Pull-ups | none on this board (the Pi's 1.8 kΩ) | |
| Cx | the AT42QT1070 accepts 1–30 pF per key | datasheet 6.2 |

**Layout:** front copper = the electrodes only. Back: U1, R1–R4, C1, C2, the J1 pads and all traces (0.25 mm signal,
0.4 mm supply), back-copper keep-outs behind the electrodes, and a tented via at each electrode's top edge. Silk lines 0.15,
JLC's minimum (0.12 until 2026-11-21).

## How to assemble
One surface-mount face, the back. Drawing: `touch-board-assembly.pdf`.
1. Bare board: VCC–GND on the HOST pads must read open.
2. Paste the back through the touch board's pattern on its stencil ([`../stencil/`](../stencil/)), keeping the squeegee
   off the strip's pattern below it (or tape it over).
   - The pattern is already mirrored to match the back seen from above, with the board lying front-down.
   - The HOST pads get no paste.
3. Place U1 (pin 1 at the chamfered corner), C1 100 nF, C2 10 µF, R1–R4 4.7 kΩ.
4. Hotplate with the front face down on a clean sheet (the front has no parts). The same paste and profile as the main
   board ([`../main-board/README.md`](../main-board/README.md)).
5. Solder the touch lead to the HOST pads with the iron: VCC, GND, SDA, SCL as labelled. The lead's four wires are
   halves of JST pre-crimped XH jumpers (ASXHSXH22K305), their contacts in an XHP-4 housing for J6 on the main board;
   free length 87 mm (harness list of 2026-11-14).

## Bring-up
VCC–GND not shorted; then, on the Pi, `sudo i2cdetect -y 1` shows **1b**.

## Earlier revisions
Rev D (set of 2026-11-09) is rev E without the wider silk and the new text; its set is in `fab/superseded/`. Rev C, the touch board of the first panel, is in [`../rev-c/`](../rev-c/). The scripts that generated rev D's
schematic and layout are in the history
([`hardware/main-board/gen/` at commit 45a38e4](https://github.com/neocleous/ha-panel/tree/45a38e49d72cf125aab3f4aa91dd065b3bc4f7ee/hardware/main-board/gen));
the KiCad files are the source.

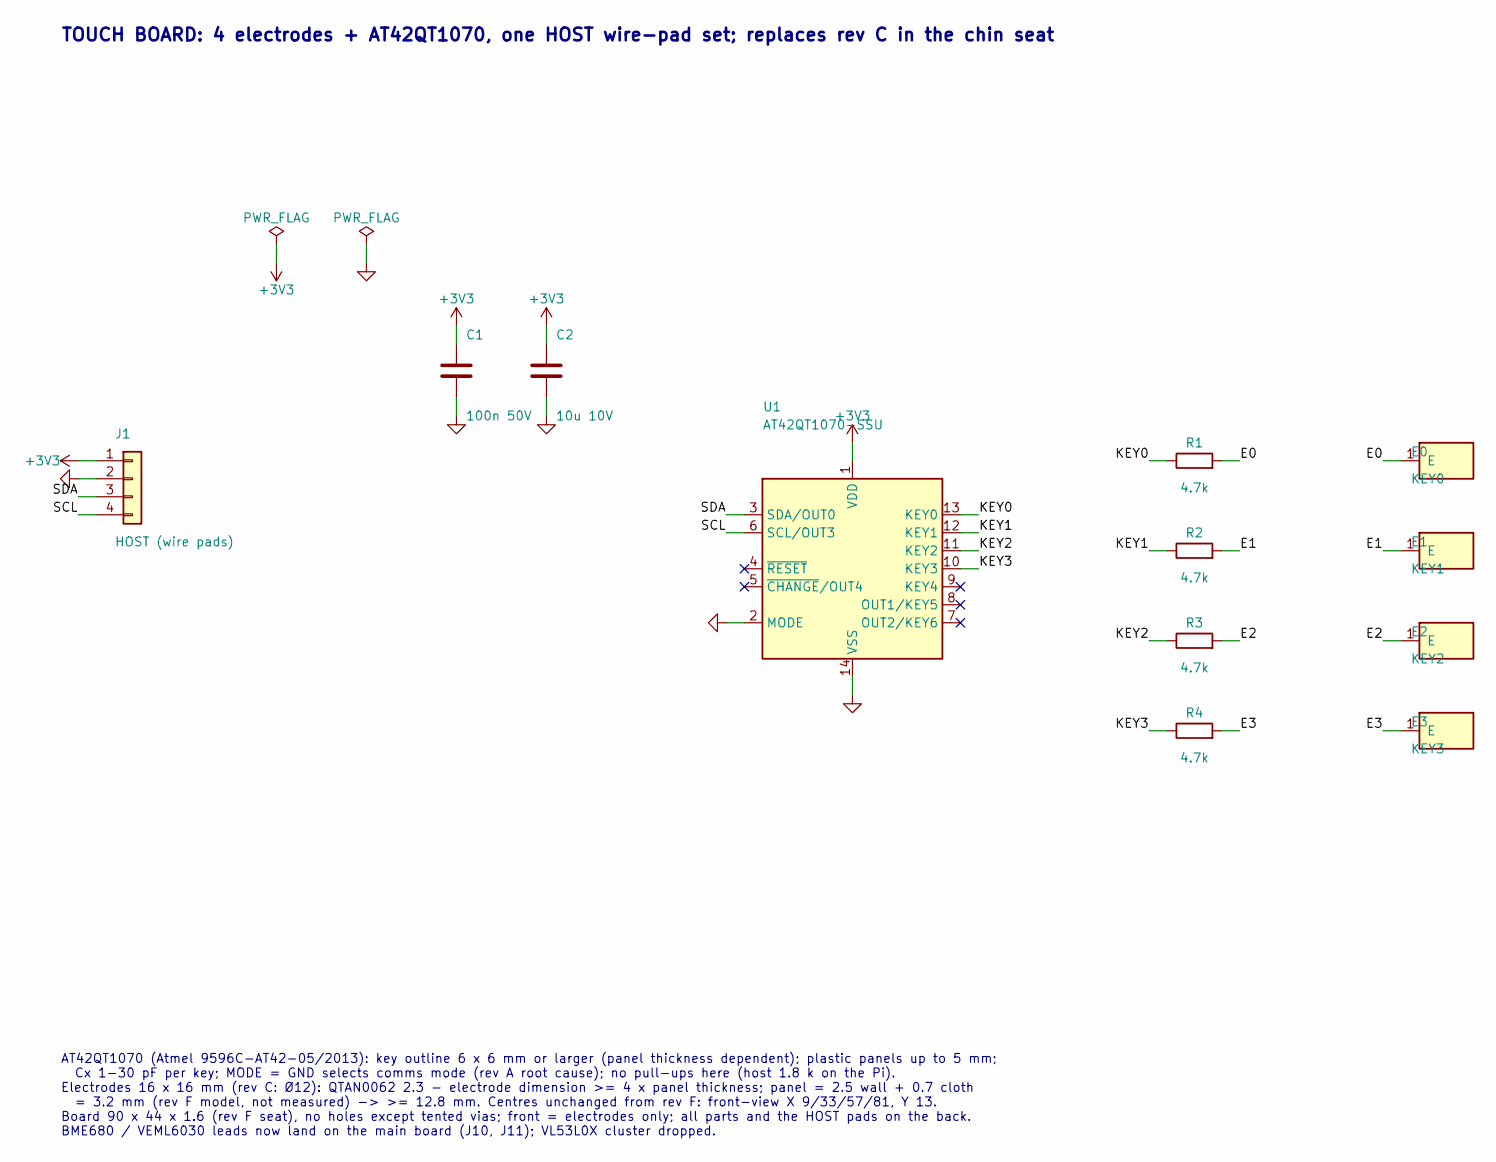
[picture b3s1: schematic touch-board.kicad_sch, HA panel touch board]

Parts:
C1: 100n 50V; C_0603_1608Metric; MPN CC0603KRX7R9BB104; DigiKey 311-1344-1-ND
C2: 10u 10V; C_0603_1608Metric; MPN EMK107BBJ106MA-T; DigiKey 587-3238-1-ND
E0: KEY0; TouchElectrode_16x16mm_R2
E1: KEY1; TouchElectrode_16x16mm_R2
E2: KEY2; TouchElectrode_16x16mm_R2
E3: KEY3; TouchElectrode_16x16mm_R2
J1: HOST (wire pads); WirePads_1x04_P3.50mm_2.0x3.0mm
R1, R2, R3, R4: 4.7k; R_0603_1608Metric; MPN RC0603FR-074K7L; DigiKey 311-4.70KHRCT-ND
U1: AT42QT1070-SSU; SOIC-14_3.9x8.7mm_P1.27mm; MPN AT42QT1070-SSUR; DigiKey none - from Daniel's stock

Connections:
+3V3: C1.1, C2.1, J1.1, U1.1 (VDD)
/E0: E0.1, R1.2
/E1: E1.1, R2.2
/E2: E2.1, R3.2
/E3: E3.1, R4.2
/KEY0: R1.1, U1.13 (KEY0)
/KEY1: R2.1, U1.12 (KEY1)
/KEY2: R3.1, U1.11 (KEY2)
/KEY3: R4.1, U1.10 (KEY3)
/SCL: J1.4, U1.6 (SCL/OUT3)
/SDA: J1.3, U1.3 (SDA/OUT0)
GND: C1.2, C2.2, J1.2, U1.2 (MODE), U1.14 (VSS)

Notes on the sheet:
TOUCH BOARD: 4 electrodes + AT42QT1070, one HOST wire-pad set; replaces rev C in the chin seat
AT42QT1070 (Atmel 9596C-AT42-05/2013): key outline 6 x 6 mm or larger (panel thickness dependent); plastic panels up to 5 mm; Cx 1-30 pF per key; MODE = GND selects comms mode (rev A root cause); no pull-ups here (host 1.8 k on the Pi). Electrodes 16 x 16 mm (rev C: Ø12): QTAN0062 2.3 - electrode d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

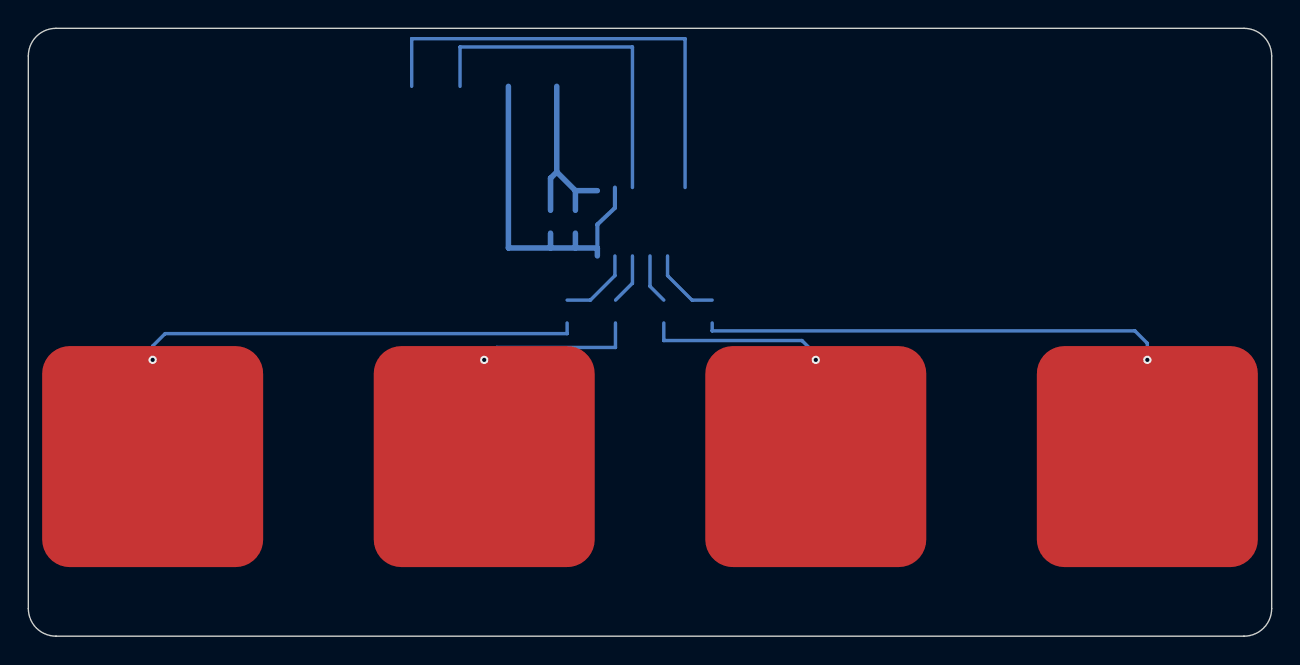
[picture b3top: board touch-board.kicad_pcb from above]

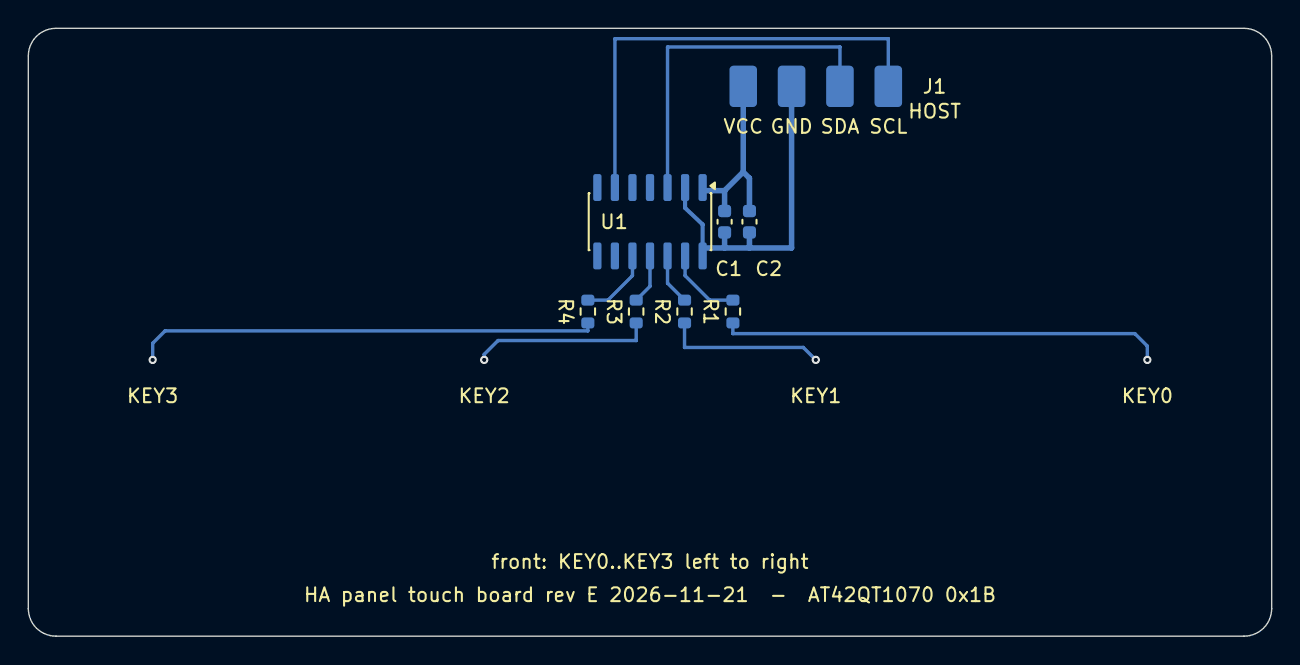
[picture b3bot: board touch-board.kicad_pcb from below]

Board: 2 copper layers, 90.0 x 44.0 mm, 12 parts (8 on the bottom side), 12 nets.
